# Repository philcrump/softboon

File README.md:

# SoftBoon

A programmable soft-start board for the Boondocker Dishy Dualie, to ease current surge at start-up.

This project is in no way associated or affiliated with Boondock Energy, Inc.

## Implementation

Small PCB designed for retrofit into an existing project.

Schematic: [img/schematic_softboon-r1.pdf](img/schematic_softboon-r1.pdf)

Dual voltage regulators allow use of 7-35V on input (Boondocker is 10-30V).

An STM32F030K6 programmable microcontroller generates the timing logic as follows:

At initial power-on:
* DC-DC and all outputs off.

When the mechanical switch input is On (open)
* Wait 1 second
* Switch the DC-DC on.
* Wait 1 second
* Switch the Dishy PoE on (and Aux Output.)
* Wait 1 second
* Switch the Router PoE on.

When the mechanical switch is Off (closed)
* Immediately switch all outputs and DC-DC off.

### Board Connections

5-pin Header J3:
* "+" (Positive Supply): Recommended to be connected after Fuse and Diode arrangement on the input of the Boondocker to benefit from Reverse Polarity protection. Can tolerate 7-35V.
* "G" (Common/Ground): "Common" on the Dishy Dualie "Remote Shutdown" header.
* Enable 0: "Router Switch" on the Dishy Dualie "Remote Shutdown" header." Can tolerate 45V open, 500mA short.
* Enable 1: "DC-DC Switch" on the Dishy Dualie "Remote Shutdown" header." Can tolerate 45V open, 500mA short.
* Enable 2: "Dishy Switch" on the Dishy Dualie "Remote Shutdown" header." Can tolerate 45V open, 500mA short.

2-pin Header J2:
* Short pins to switch unit off (optional, leave disconnected for always-on). 3.3V @ 1.1mA when shorted.

### Firmware

Written in Rust using the Embassy Framework.

NB: Optimisation and LTO is required to fit the Flash of the microcontroller.

#### Inputs

* PA3 - Switch, 3.3V open, 1.5mA closed.

#### Outputs

* PA0 - Q1 Transistor - Router Switch
* PA1 - Q2 Transistor - DC-DC
* PA2 - Q3 Transistor - Dishy

## Authors

* Phil Crump <phil@philcrump.co.uk>

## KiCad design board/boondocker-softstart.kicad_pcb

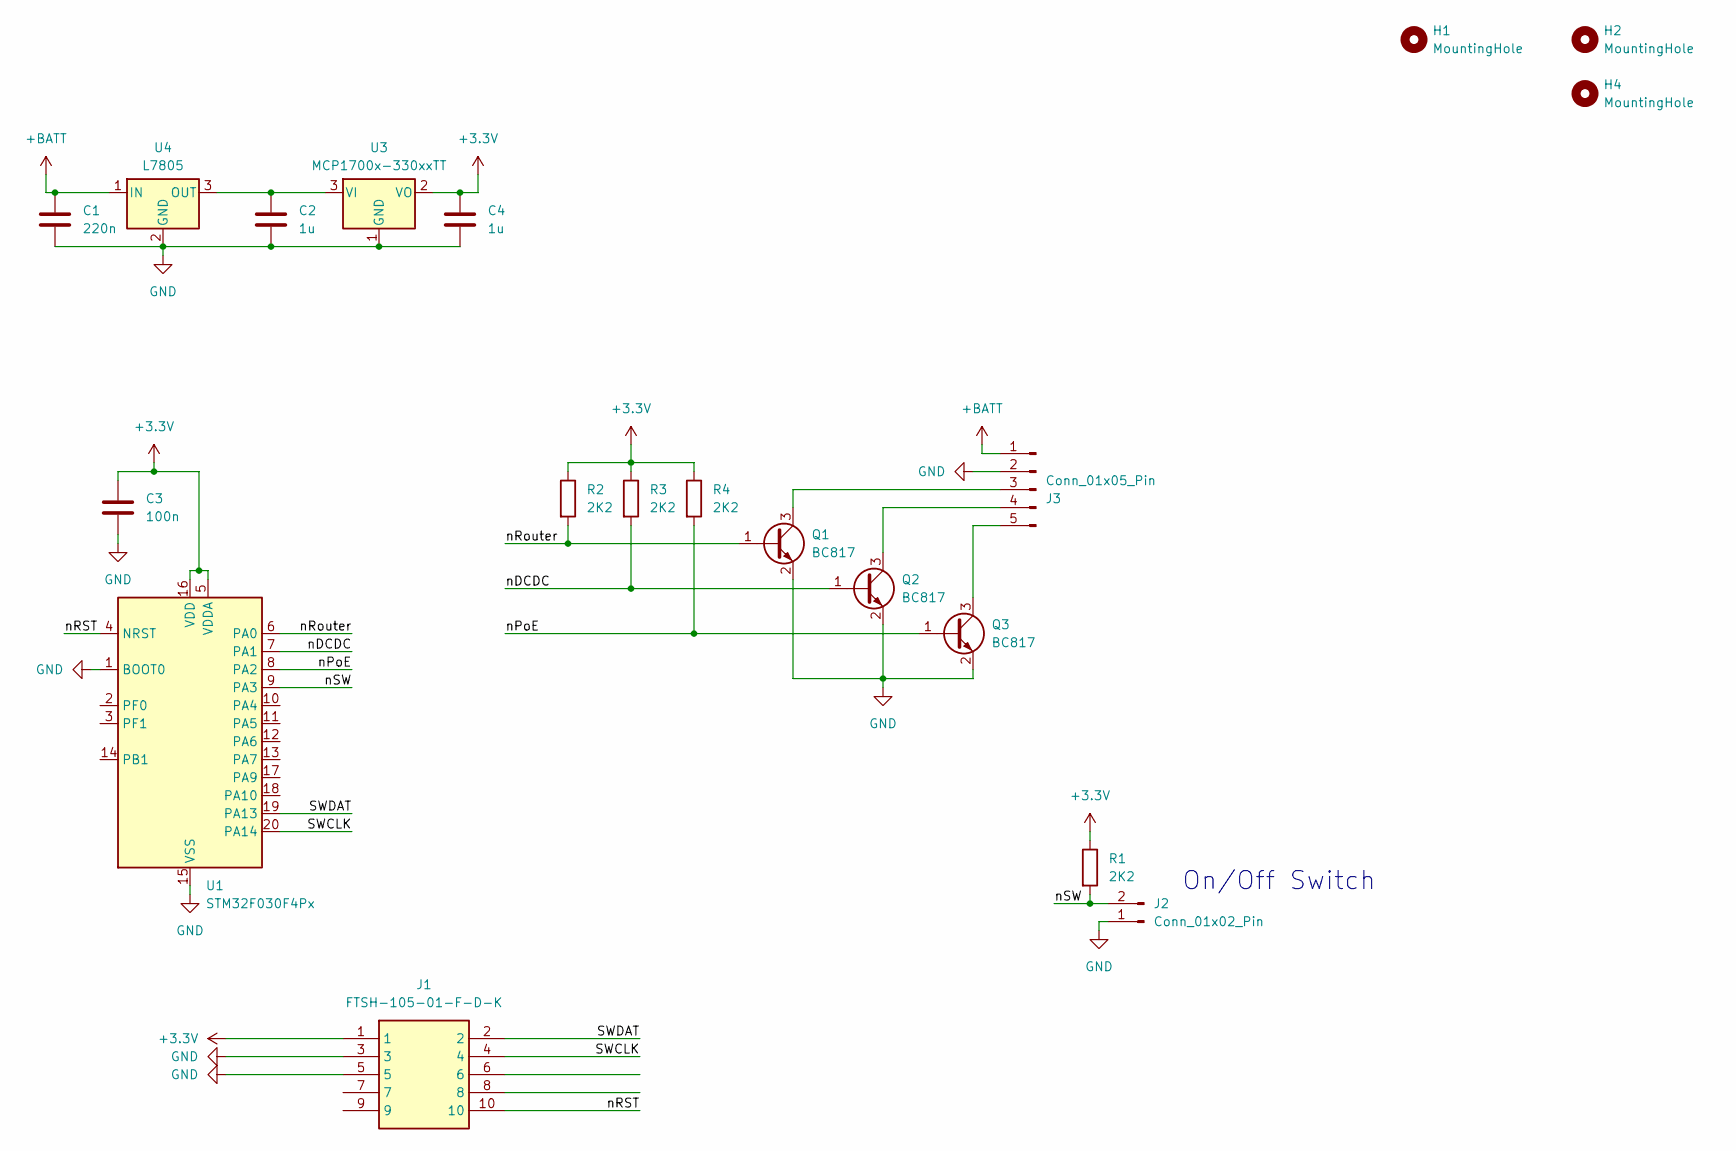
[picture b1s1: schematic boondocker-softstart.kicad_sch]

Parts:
C1: 220n; C_0603_1608Metric_Pad1.08x0.95mm_HandSolder
C2, C4: 1u; C_0603_1608Metric_Pad1.08x0.95mm_HandSolder
C3: 100n; C_0603_1608Metric_Pad1.08x0.95mm_HandSolder
H1, H2, H4: MountingHole; MountingHole_3.2mm_M3_ISO7380
J1: FTSH-105-01-F-D-K; FTSH-105-XX-YYY-D-K; Mouser Part Number 200-FTSH10501FDK
J2: Conn_01x02_Pin; Molex_KK-254_AE-6410-02A_1x02_P2.54mm_Vertical
J3: Conn_01x05_Pin; PinHeader_1x05_P2.54mm_Vertical
Q1, Q2, Q3: BC817; SOT-23
R1, R2, R3, R4: 2K2; R_0603_1608Metric_Pad0.98x0.95mm_HandSolder
U1: STM32F030F4Px; TSSOP-20_4.4x6.5mm_P0.65mm
U3: MCP1700x-330xxTT; SOT-23
U4: L7805; SOT-223-3_TabPin2

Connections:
+3.3V: C3.1, C4.1, J1.1, R1.1, R2.1, R3.1, R4.1, U1.5 (VDDA), U1.16 (VDD), U3.2 (VO)
+BATT: C1.1, J3.1, U4.1 (IN)
/SWCLK: J1.4, U1.20 (PA14)
/SWDAT: J1.2, U1.19 (PA13)
/nDCDC: Q2.1 (B), R3.2, U1.7 (PA1)
/nPoE: Q3.1 (B), R4.2, U1.8 (PA2)
/nRST: J1.10, U1.4 (NRST)
/nRouter: Q1.1 (B), R2.2, U1.6 (PA0)
/nSW: J2.2, R1.2, U1.9 (PA3)
GND: C1.2, C2.2, C3.2, C4.2, J1.3, J1.5, J2.1, J3.2, Q1.2 (E), Q2.2 (E), Q3.2 (E), U1.1 (BOOT0), U1.15 (VSS), U3.1 (GND), U4.2 (GND)
unnamed: J3.3, Q1.3 (C)
unnamed: J3.4, Q2.3 (C)
unnamed: J3.5, Q3.3 (C)
unnamed: C2.1, U3.3 (VI), U4.3 (OUT)

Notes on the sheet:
On/Off Switch

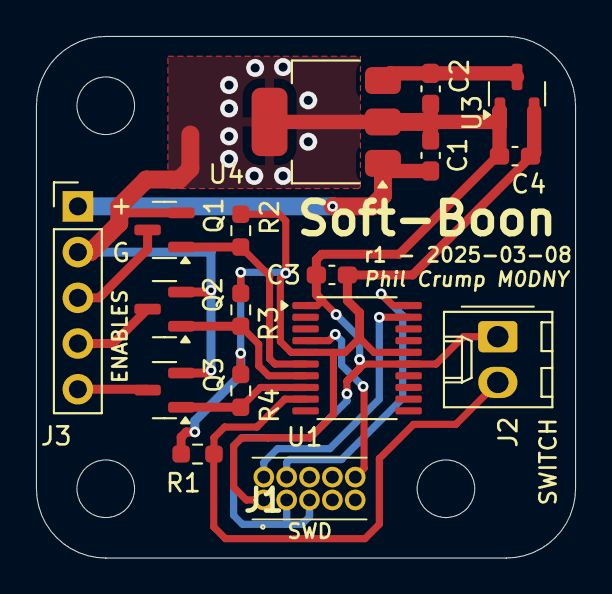
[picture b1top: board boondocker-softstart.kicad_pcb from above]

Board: 2 copper layers, 30.0 x 29.0 mm, 20 parts (0 on the bottom side), 14 nets.

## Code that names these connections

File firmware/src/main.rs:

#![no_std]
#![no_main]

use embassy_executor::Spawner;
use embassy_stm32::wdg::IndependentWatchdog;
use embassy_stm32::gpio::{Level, OutputOpenDrain, Speed, Input, Pull};
use embassy_time::{Instant, Timer};
use {defmt_rtt as _, panic_probe as _};

#[embassy_executor::main]
async fn main(_spawner: Spawner) {
    let p = embassy_stm32::init(Default::default());

    // Initialise outputs as disabled.
    let mut dcdc_disable = OutputOpenDrain::new(p.PA1, Level::High, Speed::Low);
    let mut dishy_disable = OutputOpenDrain::new(p.PA2, Level::High, Speed::Low);
    let mut router_disable = OutputOpenDrain::new(p.PA0, Level::High, Speed::Low);

    // Set up watchdog for 3 second period before reset
    let mut wdg = IndependentWatchdog::new(p.IWDG, 3_000_000);
    wdg.unleash();

    let switch_on = Input::new(p.PA3, Pull::None);

    let mut time_millis:u64 = Instant::now().as_millis();

    let mut state: u32 = 0;
    let mut state_time_millis:u64 = time_millis;

    // Always keep outputs disabled for 1 second at initial power-on
    Timer::after_millis(1000).await;

    loop {
        time_millis = Instant::now().as_millis();

        if switch_on.is_high() {
            if state == 0 {
                dcdc_disable.set_low();

                state = 1;
                state_time_millis = time_millis;
            }
            else if state == 1 && (time_millis - state_time_millis) > 1000 {
                dishy_disable.set_low();

                state = 2;
                state_time_millis = time_millis;
            }
            else if state == 2 && (time_millis - state_time_millis) > 1000 {
                router_disable.set_low();

                state = 3;
                state_time_millis = time_millis;
            }
        }
        else {
            router_disable.set_high();
            dishy_disable.set_high();
            dcdc_disable.set_high();

            state = 0;
            state_time_millis = time_millis;
        }

        Timer::after_millis(10).await;
        wdg.pet();
    }
}

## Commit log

2025-09-20 Initial commit.
2025-09-20 README: Fix image paths.
